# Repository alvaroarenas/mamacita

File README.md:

# Mamacita keyboard

The Mamamcita keyboard is a split keyboard with 4x6 column staggered keys and 4 thumb keys,
based on the  [Corne keyboard](https://github.com/foostan/crkbd).

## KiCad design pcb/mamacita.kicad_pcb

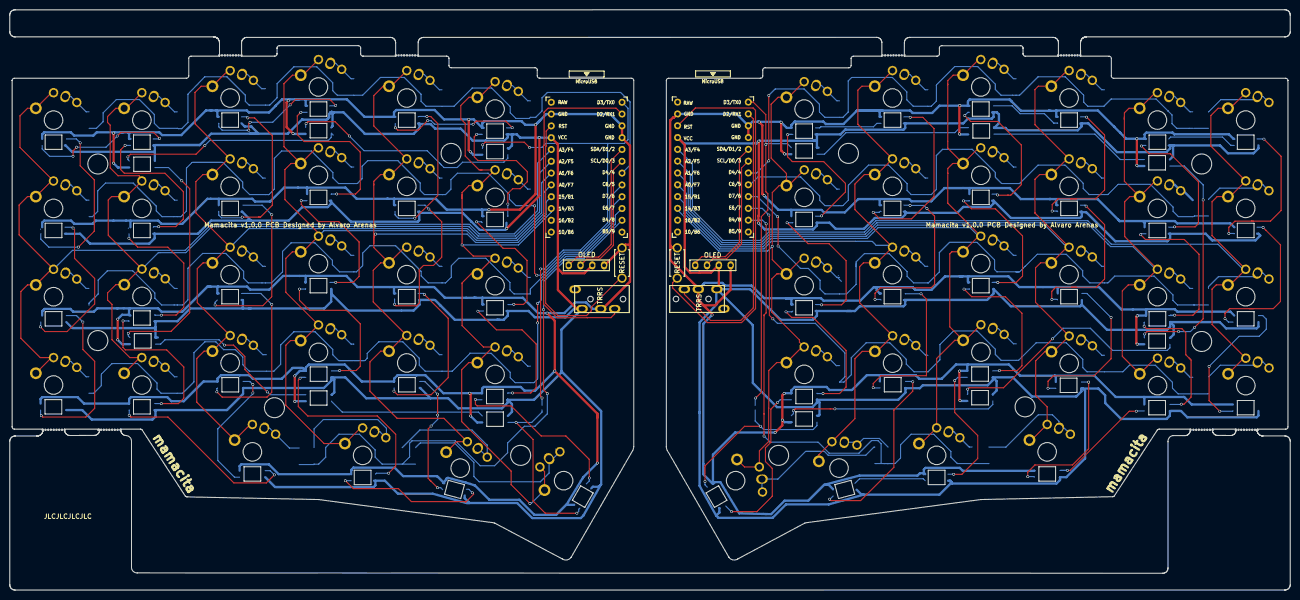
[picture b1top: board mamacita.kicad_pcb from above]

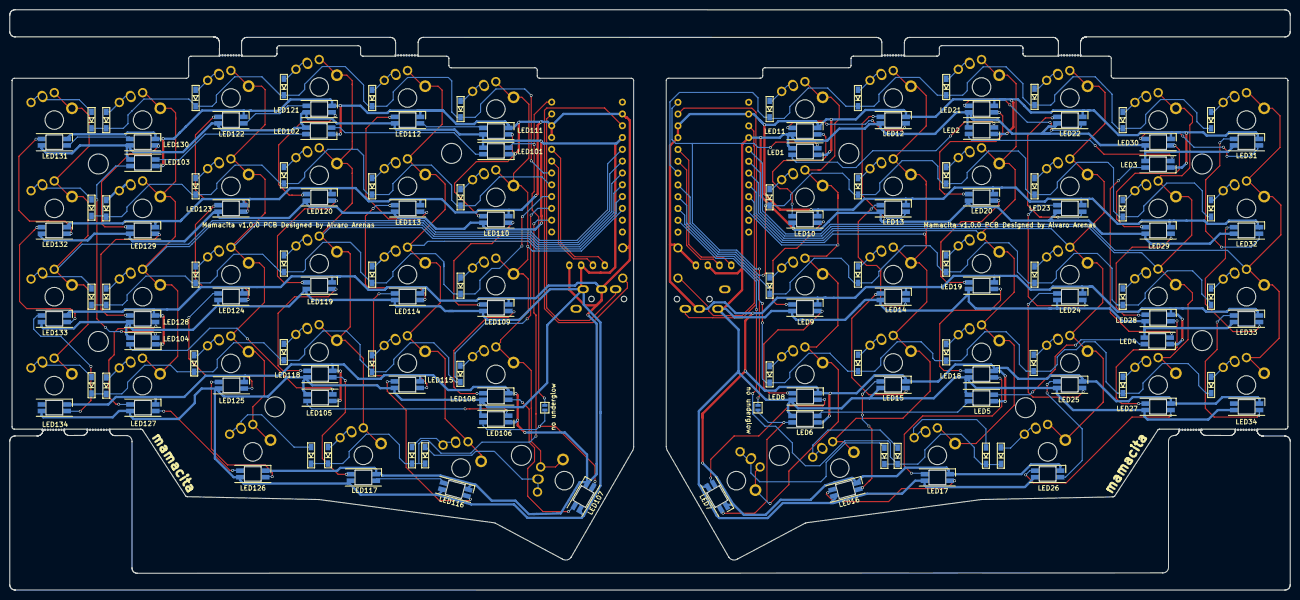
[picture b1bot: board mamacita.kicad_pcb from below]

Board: 2 copper layers, 275.5 x 124.9 mm, 200 parts (126 on the bottom side), 158 nets.

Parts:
D1, D2, D3, D4, D5, D6, D7, D8, D9, D10, D11, D12, D13, D14, D15, D16, D17, D18, D19, D20, D21, D22, D23, D24, D25, D26, D27, D28, D101, D102, D103, D104, D105, D106, D107, D108, D109, D110, D111, D112, D113, D114, D115, D116, D117, D118, D119, D120, D121, D122, D123, D124, D125, D126, D127, D128: D; D3_SMD_v2
H1, H1r, H2, H2r, H3, H3r, H4, H4r, H5, H5r: M2_HOLE_v2
J1, J3: MJ-4PP-9; MJ-4PP-9_1side
J2, J4: OLED; OLED_1side
JP1, JP2: no underglow; Jumper
LED1, LED2, LED3, LED4, LED5, LED6, LED101, LED102, LED103, LED104, LED105, LED106: MINI-E_underglow; YS-SK6812MINI-E_underglow
LED7, LED8, LED9, LED10, LED11, LED12, LED13, LED14, LED15, LED16, LED17, LED18, LED19, LED20, LED21, LED22, LED23, LED24, LED25, LED26, LED27, LED28, LED29, LED30, LED31, LED32, LED33, LED34, LED107, LED108, LED109, LED110, LED111, LED112, LED113, LED114, LED115, LED116, LED117, LED118, LED119, LED120, LED121, LED122, LED123, LED124, LED125, LED126, LED127, LED128, LED129, LED130, LED131, LED132, LED133, LED134: MINI-E; YS-SK6812MINI-E
RSW1, RSW2: SW_PUSH; ResetSW_1side
SW1, SW2, SW3, SW4, SW5, SW6, SW7, SW8, SW9, SW10, SW11, SW12, SW13, SW14, SW15, SW16, SW17, SW18, SW19, SW20, SW21, SW22, SW23, SW24, SW25, SW26, SW27, SW28, SW101, SW102, SW103, SW104, SW105, SW106, SW107, SW108, SW109, SW110, SW111, SW112, SW113, SW114, SW115, SW116, SW117, SW118, SW119, SW120, SW121, SW122, SW123, SW124, SW125, SW126, SW127, SW128: SW_PUSH; MX100Choc_fixed
U1, U2: ProMicro; ProMicro_v3

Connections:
GND: J1.C, J2.4, LED1.3, LED2.3, LED3.3, LED4.3, LED5.3, LED6.3, LED7.3, LED8.3, LED9.3, LED10.3, LED11.3, LED12.3, LED13.3, LED14.3, LED15.3, LED16.3, LED17.3, LED18.3, LED19.3, LED20.3, LED21.3, LED22.3, LED23.3, LED24.3, LED25.3, LED26.3, LED27.3, LED28.3, LED29.3, LED30.3, LED31.3, LED32.3, LED33.3, LED34.3, RSW1.2, U1.3, U1.4, U1.23
GNDA: J3.C, J4.4, LED101.3, LED102.3, LED103.3, LED104.3, LED105.3, LED106.3, LED107.3, LED108.3, LED109.3, LED110.3, LED111.3, LED112.3, LED113.3, LED114.3, LED115.3, LED116.3, LED117.3, LED118.3, LED119.3, LED120.3, LED121.3, LED122.3, LED123.3, LED124.3, LED125.3, LED126.3, LED127.3, LED128.3, LED129.3, LED130.3, LED131.3, LED132.3, LED133.3, LED134.3, RSW2.2, U2.3, U2.4, U2.23
LED: JP1.1, LED1.4, U1.1
LED_r: JP2.1, LED101.4, U2.1
unnamed: D1.2, SW1.2
unnamed: D2.2, SW2.2
unnamed: D3.2, SW3.2
unnamed: D4.2, SW4.2
unnamed: D5.2, SW5.2
unnamed: D6.2, SW6.2
unnamed: D7.2, SW7.2
unnamed: D8.2, SW8.2
unnamed: D9.2, SW9.2
unnamed: D10.2, SW10.2
unnamed: D11.2, SW11.2
unnamed: D12.2, SW12.2
unnamed: D13.2, SW13.2
unnamed: D14.2, SW14.2
unnamed: D15.2, SW15.2
unnamed: D16.2, SW16.2
unnamed: D17.2, SW17.2
unnamed: D18.2, SW18.2
unnamed: D19.2, SW19.2
unnamed: D20.2, SW20.2
unnamed: D21.2, SW21.2
unnamed: D22.2, SW22.2
unnamed: D23.2, SW23.2
unnamed: D24.2, SW24.2
unnamed: D25.2, SW25.2
unnamed: D26.2, SW26.2
unnamed: D27.2, SW27.2
unnamed: D28.2, SW28.2
unnamed: D101.2, SW101.2
unnamed: D102.2, SW102.2
unnamed: D103.2, SW103.2
unnamed: D104.2, SW104.2
unnamed: D105.2, SW105.2
unnamed: D106.2, SW106.2
unnamed: D107.2, SW107.2
unnamed: D108.2, SW108.2
unnamed: D109.2, SW109.2
unnamed: D110.2, SW110.2
unnamed: D111.2, SW111.2
unnamed: D112.2, SW112.2
unnamed: D113.2, SW113.2
unnamed: D114.2, SW114.2
unnamed: D115.2, SW115.2
unnamed: D116.2, SW116.2
unnamed: D117.2, SW117.2
unnamed: D118.2, SW118.2
unnamed: D119.2, SW119.2
unnamed: D120.2, SW120.2
unnamed: D121.2, SW121.2
unnamed: D122.2, SW122.2
unnamed: D123.2, SW123.2
unnamed: D124.2, SW124.2
unnamed: D125.2, SW125.2
unnamed: D126.2, SW126.2
unnamed: D127.2, SW127.2
unnamed: D128.2, SW128.2
unnamed: JP1.2, LED6.2, LED7.4
unnamed: JP2.2, LED106.2, LED107.4
unnamed: LED1.2, LED2.4
unnamed: LED2.2, LED3.4
unnamed: LED3.2, LED4.4
unnamed: LED4.2, LED5.4
unnamed: LED5.2, LED6.4
unnamed: LED7.2, LED8.4
unnamed: LED8.2, LED9.4
unnamed: LED10.2, LED11.4
unnamed: LED9.2, LED10.4
unnamed: LED11.2, LED12.4
unnamed: LED12.2, LED13.4
unnamed: LED13.2, LED14.4
unnamed: LED14.2, LED15.4
unnamed: LED15.2, LED16.4
unnamed: LED16.2, LED17.4
unnamed: LED17.2, LED18.4
unnamed: LED18.2, LED19.4
unnamed: LED19.2, LED20.4
unnamed: LED20.2, LED21.4
unnamed: LED21.2, LED22.4
unnamed: LED22.2, LED23.4
unnamed: LED23.2, LED24.4
unnamed: LED24.2, LED25.4
unnamed: LED25.2, LED26.4
unnamed: LED26.2, LED27.4
unnamed: LED27.2, LED28.4
unnamed: LED28.2, LED29.4
unnamed: LED29.2, LED30.4
unnamed: LED30.2, LED31.4
unnamed: LED31.2, LED32.4
unnamed: LED32.2, LED33.4
unnamed: LED33.2, LED34.4
unnamed: LED101.2, LED102.4
unnamed: LED102.2, LED103.4
unnamed: LED103.2, LED104.4
unnamed: LED104.2, LED105.4
unnamed: LED105.2, LED106.4
unnamed: LED107.2, LED108.4
unnamed: LED108.2, LED109.4
unnamed: LED109.2, LED110.4
unnamed: LED110.2, LED111.4
unnamed: LED111.2, LED112.4
unnamed: LED112.2, LED113.4
unnamed: LED113.2, LED114.4
unnamed: LED114.2, LED115.4
unnamed: LED115.2, LED116.4
unnamed: LED116.2, LED117.4
unnamed: LED117.2, LED118.4
unnamed: LED118.2, LED119.4
unnamed: LED119.2, LED120.4
unnamed: LED120.2, LED121.4
unnamed: LED121.2, LED122.4
unnamed: LED122.2, LED123.4
unnamed: LED123.2, LED124.4
unnamed: LED124.2, LED125.4
unnamed: LED125.2, LED126.4
unnamed: LED126.2, LED127.4
unnamed: LED127.2, LED128.4
unnamed: LED128.2, LED129.4
unnamed: LED129.2, LED130.4
unnamed: LED130.2, LED131.4
unnamed: LED131.2, LED132.4
unnamed: LED132.2, LED133.4
unnamed: LED133.2, LED134.4
SCL: J2.2, U1.6
SCL_r: J4.2, U2.6
SDA: J2.1, U1.5
SDA_r: J4.1, U2.5
VCC: J1.D, J2.3, LED1.1, LED2.1, LED3.1, LED4.1, LED5.1, LED6.1, LED7.1, LED8.1, LED9.1, LED10.1, LED11.1, LED12.1, LED13.1, LED14.1, LED15.1, LED16.1, LED17.1, LED18.1, LED19.1, LED20.1, LED21.1, LED22.1, LED23.1, LED24.1, LED25.1, LED26.1, LED27.1, LED28.1, LED29.1, LED30.1, LED31.1, LED32.1, LED33.1, LED34.1, U1.21
VDD: J3.D, J4.3, LED101.1, LED102.1, LED103.1, LED104.1, LED105.1, LED106.1, LED107.1, LED108.1, LED109.1, LED110.1, LED111.1, LED112.1, LED113.1, LED114.1, LED115.1, LED116.1, LED117.1, LED118.1, LED119.1, LED120.1, LED121.1, LED122.1, LED123.1, LED124.1, LED125.1, LED126.1, LED127.1, LED128.1, LED129.1, LED130.1, LED131.1, LED132.1, LED133.1, LED134.1, U2.21
col0: SW1.1, SW7.1, SW13.1, SW19.1, U1.20
col0_r: SW101.1, SW107.1, SW113.1, SW119.1, U2.20
col1: SW2.1, SW8.1, SW14.1, SW20.1, U1.19
col1_r: SW102.1, SW108.1, SW114.1, SW120.1, U2.19
col2: SW3.1, SW9.1, SW15.1, SW21.1, SW25.1, U1.18
col2_r: SW103.1, SW109.1, SW115.1, SW121.1, SW125.1, U2.18
col3: SW4.1, SW10.1, SW16.1, SW22.1, SW26.1, U1.17
col3_r: SW104.1, SW110.1, SW116.1, SW122.1, SW126.1, U2.17
col4: SW5.1, SW11.1, SW17.1, SW23.1, SW27.1, U1.16
col4_r: SW105.1, SW111.1, SW117.1, SW123.1, SW127.1, U2.16
col5: SW6.1, SW12.1, SW18.1, SW24.1, SW28.1, U1.15
col5_r: SW106.1, SW112.1, SW118.1, SW124.1, SW128.1, U2.15
data: J1.B, U1.2
data_r: J3.B, U2.2
reset: RSW1.1, U1.22
reset_r: RSW2.1, U2.22
row0: D1.1, D2.1, D3.1, D4.1, D5.1, D6.1, U1.7
row0_r: D101.1, D102.1, D103.1, D104.1, D105.1, D106.1, U2.7
row1: D7.1, D8.1, D9.1, D10.1, D11.1, D12.1, U1.8
row1_r: D107.1, D108.1, D109.1, D110.1, D111.1, D112.1, U2.8
row2: D13.1, D14.1, D15.1, D16.1, D17.1, D18.1, U1.9
row2_r: D113.1, D114.1, D115.1, D116.1, D117.1, D118.1, U2.9
row3: D19.1, D20.1, D21.1, D22.1, D23.1, D24.1, U1.10
row3_r: D119.1, D120.1, D121.1, D122.1, D123.1, D124.1, U2.10
row4: D25.1, D26.1, D27.1, D28.1, U1.11
row4_r: D125.1, D126.1, D127.1, D128.1, U2.11

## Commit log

2021-02-27 Project initialization v1.0
